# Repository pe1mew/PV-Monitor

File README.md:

# PV-Monitor
A monitor for small PV installations

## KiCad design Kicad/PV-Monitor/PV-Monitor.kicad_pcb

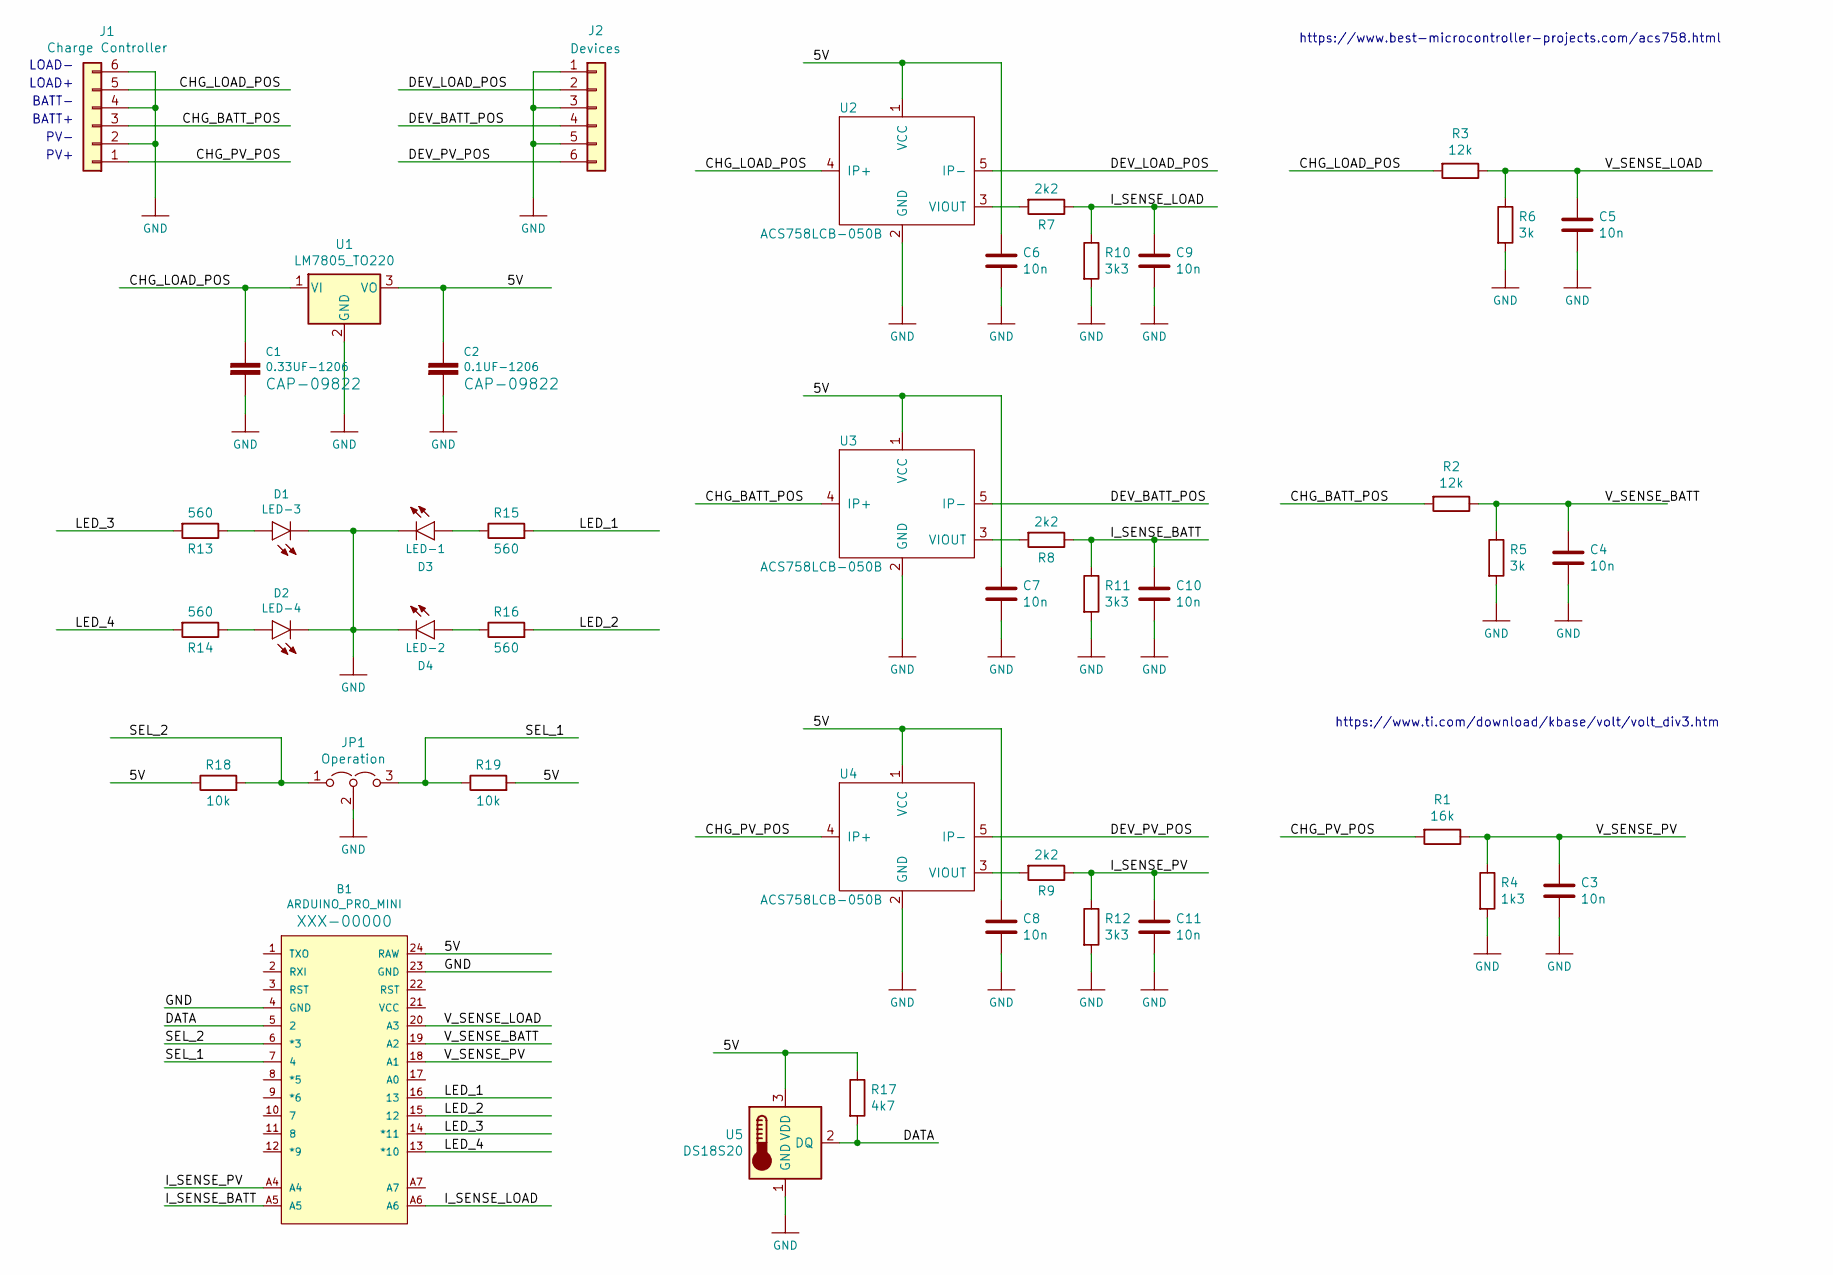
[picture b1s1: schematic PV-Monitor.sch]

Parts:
B1: ARDUINO_PRO_MINI
C1: 0.33UF-1206; C_1206_3216Metric_Pad1.42x1.75mm_HandSolder
C2: 0.1UF-1206; C_1206_3216Metric_Pad1.42x1.75mm_HandSolder
C3, C4, C5, C6, C7, C8, C9, C10, C11: 10n; C_1206_3216Metric
D1: LED-3; LED-1206
D2: LED-4; LED-1206
D3: LED-1; LED-1206
D4: LED-2; LED-1206
J1: Charge Controller; Molex_Mini-Fit_Sr_42819-62XX_1x06_P10.00mm_Vertical_Thermal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
J2: Devices; Molex_Mini-Fit_Sr_42819-62XX_1x06_P10.00mm_Vertical_Thermal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
JP1: Operation; PinHeader_1x03_P2.54mm_Vertical
R1: 16k; R_1206_3216Metric_Pad1.42x1.75mm_HandSolder
R2, R3: 12k; R_1206_3216Metric_Pad1.42x1.75mm_HandSolder
R4: 1k3; R_1206_3216Metric_Pad1.42x1.75mm_HandSolder
R5, R6: 3k; R_1206_3216Metric_Pad1.42x1.75mm_HandSolder
R7, R8, R9: 2k2; R_1206_3216Metric_Pad1.42x1.75mm_HandSolder
R10, R11, R12: 3k3; R_1206_3216Metric_Pad1.42x1.75mm_HandSolder
R13, R14, R15, R16: 560; R_1206_3216Metric_Pad1.42x1.75mm_HandSolder
R17: 4k7; R_1206_3216Metric_Pad1.42x1.75mm_HandSolder
R18, R19: 10k; R_1206_3216Metric_Pad1.42x1.75mm_HandSolder
U1: LM7805_TO220; TO-220-3_Vertical
U2, U3, U4: ACS758LCB-050B
U5: DS18S20; TO-92_Inline

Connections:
/5V: B1.24 (RAW), C2.1, C6.1, C7.1, C8.1, R17.1, R18.1, R19.2, U1.3 (VO), U2.1 (VCC), U3.1 (VCC), U4.1 (VCC), U5.3 (VDD)
/CHG_BATT_POS: J1.3, R2.2, U3.4 (IP+)
/CHG_LOAD_POS: C1.1, J1.5, R3.2, U1.1 (VI), U2.4 (IP+)
/CHG_PV_POS: J1.1, R1.2, U4.4 (IP+)
/DATA: B1.5 (2), R17.2, U5.2 (DQ)
/DEV_BATT_POS: J2.4, U3.5 (IP-)
/DEV_LOAD_POS: J2.2, U2.5 (IP-)
/DEV_PV_POS: J2.6, U4.5 (IP-)
/I_SENSE_BATT: B1.A5, C10.1, R8.1, R11.1
/I_SENSE_LOAD: B1.A6, C9.1, R7.1, R10.1
/I_SENSE_PV: B1.A4, C11.1, R9.1, R12.1
/LED_1: B1.16 (13), R15.2
/LED_2: B1.15 (12), R16.2
/LED_3: B1.14 (*11), R13.2
/LED_4: B1.13 (*10), R14.2
/SEL_1: B1.7 (4), JP1.3 (B), R19.1
/SEL_2: B1.6 (*3), JP1.1 (A), R18.2
/V_SENSE_BATT: B1.19 (A2), C4.1, R2.1, R5.1
/V_SENSE_LOAD: B1.20 (A3), C5.1, R3.1, R6.1
/V_SENSE_PV: B1.18 (A1), C3.1, R1.1, R4.1
GND: B1.4 (GND), B1.23 (GND), C1.2, C2.2, C3.2, C4.2, C5.2, C6.2, C7.2, C8.2, C9.2, C10.2, C11.2, D1.C, D2.C, D3.C, D4.C, J1.2, J1.4, J1.6, J2.1, J2.3, J2.5, JP1.2 (C), R4.2, R5.2, R6.2, R10.2, R11.2, R12.2, U1.2 (GND), U2.2 (GND), U3.2 (GND), U4.2 (GND), U5.1 (GND)
unnamed: D1.A, R13.1
unnamed: D2.A, R14.1
unnamed: D3.A, R15.1
unnamed: D4.A, R16.1
unnamed: R7.2, U2.3 (VIOUT)
unnamed: R8.2, U3.3 (VIOUT)
unnamed: R9.2, U4.3 (VIOUT)

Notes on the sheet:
PV+
PV-
BATT+
BATT-
LOAD+
LOAD-
https://www.ti.com/download/kbase/volt/volt_div3.htm
https://www.best-microcontroller-projects.com/acs758.html

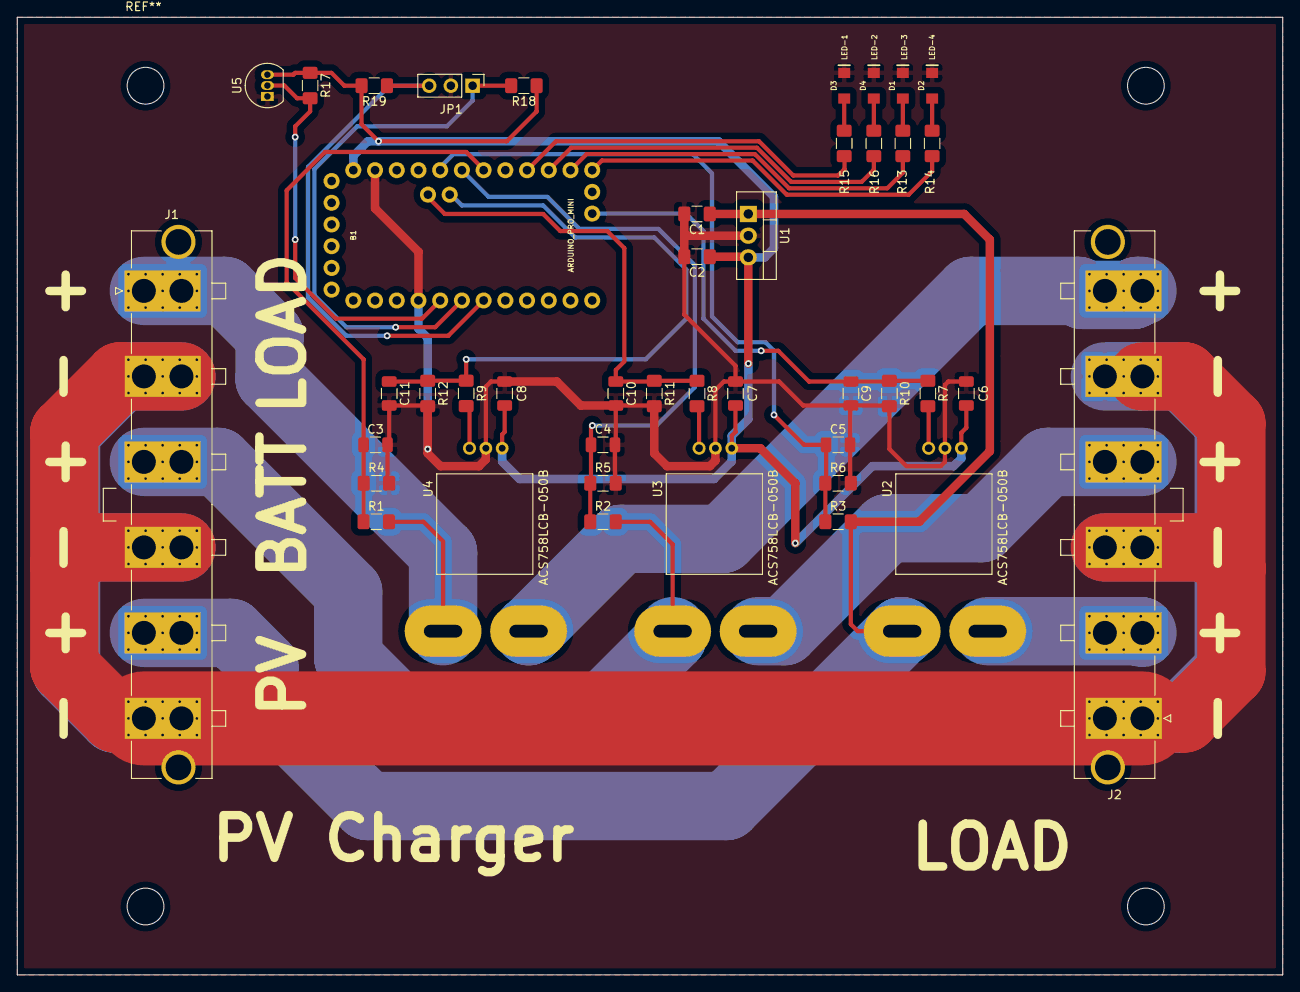
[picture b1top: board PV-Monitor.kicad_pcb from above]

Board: 2 copper layers, 148.0 x 112.0 mm, 43 parts (0 on the bottom side), 28 nets.

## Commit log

2021-01-01 Added storage class
2021-04-14 Added initial software development
